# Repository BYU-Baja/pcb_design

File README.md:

# pcb_design
Design files for our custom PCB's including datasheets and custom footprints

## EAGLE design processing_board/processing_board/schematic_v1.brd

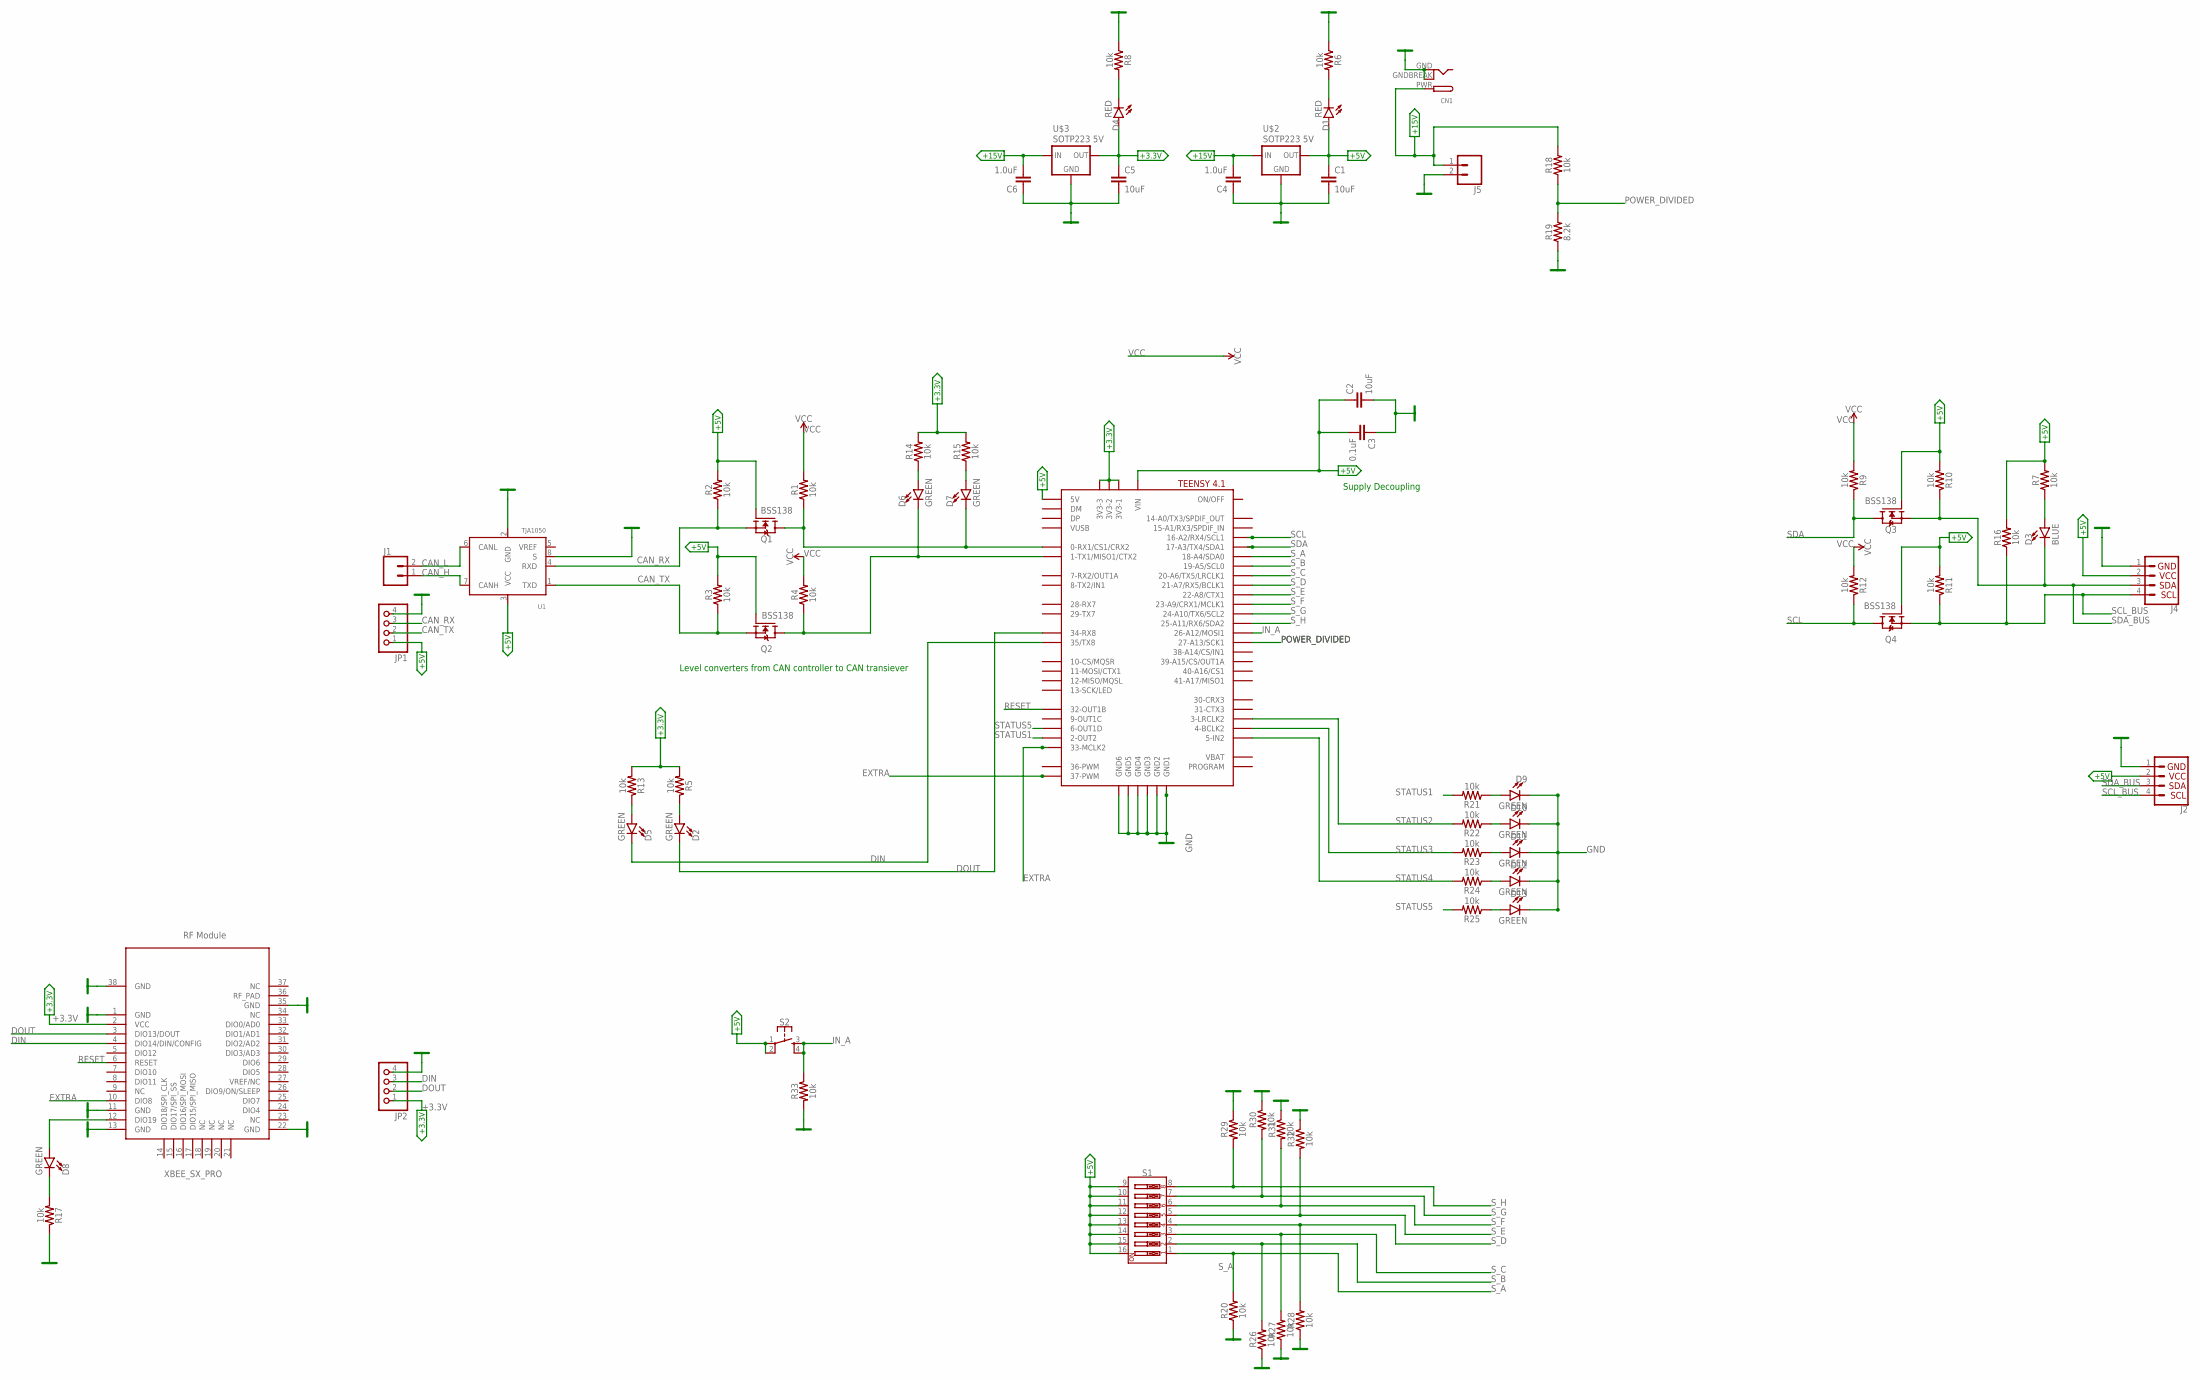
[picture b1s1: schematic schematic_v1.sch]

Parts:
C1, C2, C5: 10uF; 0603
C3: 0.1uF; 0603
C4, C6: 1.0uF; 0603
CN1: DCBARRELPTH; DCJACK_2MM_PTH
D1, D4: RED; LED-0603
D2, D5, D6, D7, D8, D9, D10, D11, D12, D13: GREEN; LED-0603
D3: BLUE; LED-0603
J1: CONN_02; 1X02
J2, J4: I2C_STANDARD; 1X04
J5: CONN_02LOCK_LONGPADS; 1X02_LOCK_LONGPADS
JP1, JP2: PINHD-1X4; 1X04
Q1, Q2, Q3, Q4: BSS138; SOT95P240X111-3N
R1, R2, R3, R4, R5, R6, R7, R8, R9, R10, R11, R12, R13, R14, R15, R16, R17, R18, R20, R21, R22, R23, R24, R25, R26, R27, R28, R29, R30, R31, R32, R33: 10k; 0603
R19: 8.2k; 0603
S1: DIP-08-PTH; DIPSWITCH-08
S2: MOMENTARY-SWITCH-SPST-2-SMD-5.2MM; TACTILE_SWITCH_SMD_5.2MM
U1: TJA1050; SOT96-1
U$1: XBEE_SX_PRO
U$2, U$3: SOTP223 5V; SOT223
U$4: TEENSY41-E; TENNSY41-E

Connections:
+3.3V: C5.1, D4.A, JP2.1, R5.2, R13.2, R14.2, R15.2, U$1.2 (VCC), U$3.2 (OUT), U$4.3V3-1, U$4.3V3-2, U$4.3V3-3
+5V: C1.1, C2.1, C3.2, D1.A, J2.2, J4.2, JP1.1, Q1.1 (G), Q2.1 (G), Q3.1 (G), Q4.1 (G), R2.2, R3.2, R7.2, R10.2, R11.2, R16.2, S1.9, S1.10, S1.11, S1.12, S1.13, S1.14, S1.15, S1.16, S2.1, S2.2, U1.3 (VCC), U$2.2 (OUT), U$4.+5V (5V), U$4.VIN
+15V: C4.2, C6.2, CN1.PWR, J5.1, R18.2, U$2.3 (IN), U$3.3 (IN)
CAN_H: J1.1, U1.7 (CANH)
CAN_L: J1.2, U1.6 (CANL)
CAN_RX: JP1.3, Q1.2 (S), R2.1, U1.4 (RXD)
CAN_TX: JP1.2, Q2.2 (S), R3.1, U1.1 (TXD)
DIN: D5.C, JP2.3, U$1.4 (DIO14/DIN/CONFIG), U$4.35-TX8 (35/TX8)
DOUT: D2.C, JP2.2, U$1.3 (DIO13/DOUT), U$4.34-RX8
EXTRA: U$1.10 (DIO8), U$4.33-MCLK2
GND: C1.2, C2.2, C3.1, C4.1, C5.2, C6.1, CN1.GND, CN1.GNDBREAK, D9.C, D10.C, D11.C, D12.C, D13.C, J2.1, J4.1, J5.2, JP1.4, JP2.4, R6.1, R8.1, R17.1, R19.1, R20.1, R26.1, R27.1, R28.1, R29.1, R30.1, R31.1, R32.1, R33.2, U1.2 (GND), U1.8 (S), U$1.1 (GND), U$1.11 (GND), U$1.13 (GND), U$1.22 (GND), U$1.35 (GND), U$1.38 (GND), U$2.1 (GND), U$3.1 (GND), U$4.GND1, U$4.GND2, U$4.GND3, U$4.GND4, U$4.GND5, U$4.GND6
IN_A: R33.1, S2.3, S2.4, U$4.26-A12/MOSI1
unnamed: D3.A, R7.1
unnamed: D7.C, Q1.3 (D), R1.1, U$4.0-RX1/CS1/CRX2
unnamed: D5.A, R13.1
unnamed: D1.C, R6.2
unnamed: D2.A, R5.1
unnamed: D4.C, R8.2
unnamed: D6.C, Q2.3 (D), R4.1, U$4.1-TX1/MISO1/CTX2
unnamed: D8.A, U$1.12 (DIO19)
unnamed: D7.A, R15.1
unnamed: D6.A, R14.1
unnamed: D9.A, R21.1
unnamed: D10.A, R22.1
unnamed: D11.A, R23.1
unnamed: D12.A, R24.1
unnamed: D13.A, R25.1
unnamed: D8.C, R17.2
POWER_DIVIDED: R18.1, R19.2, U$4.27-A13/SCK1
RESET: U$1.6 (RESET), U$4.32-OUT1B
SCL: Q4.3 (D), R12.1, U$4.16-A2/RX4/SCL1
SCL_BUS: J2.4, J4.4, Q4.2 (S), R11.1, R16.1
SDA: Q3.3 (D), R9.1, U$4.17-A3/TX4/SDA1
SDA_BUS: D3.C, J2.3, J4.3, Q3.2 (S), R10.1
STATUS1: R21.2, U$4.2-OUT2
STATUS2: R22.2, U$4.3-LRCLK2
STATUS3: R23.2, U$4.4-BCLK2
STATUS4: R24.2, U$4.5-IN2
STATUS5: R25.2, U$4.6-OUT1D
S_A: R20.2, S1.1, U$4.18-A4/SDA0
S_B: R26.2, S1.2, U$4.19-A5/SCL0
S_C: R27.2, S1.3, U$4.20-A6/TX5/LRCLK1
S_D: R28.2, S1.4, U$4.21-A7/RX5/BCLK1
S_E: R32.2, S1.5, U$4.22-A8/CTX1
S_F: R31.2, S1.6, U$4.23-A9/CRX1/MCLK1
S_G: R30.2, S1.7, U$4.24-A10/TX6/SCL2
S_H: R29.2, S1.8, U$4.25-A11/RX6/SDA2
VCC: R1.2, R4.2, R9.2, R12.2

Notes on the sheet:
Supply Decoupling
Level converters from CAN controller to CAN transiever

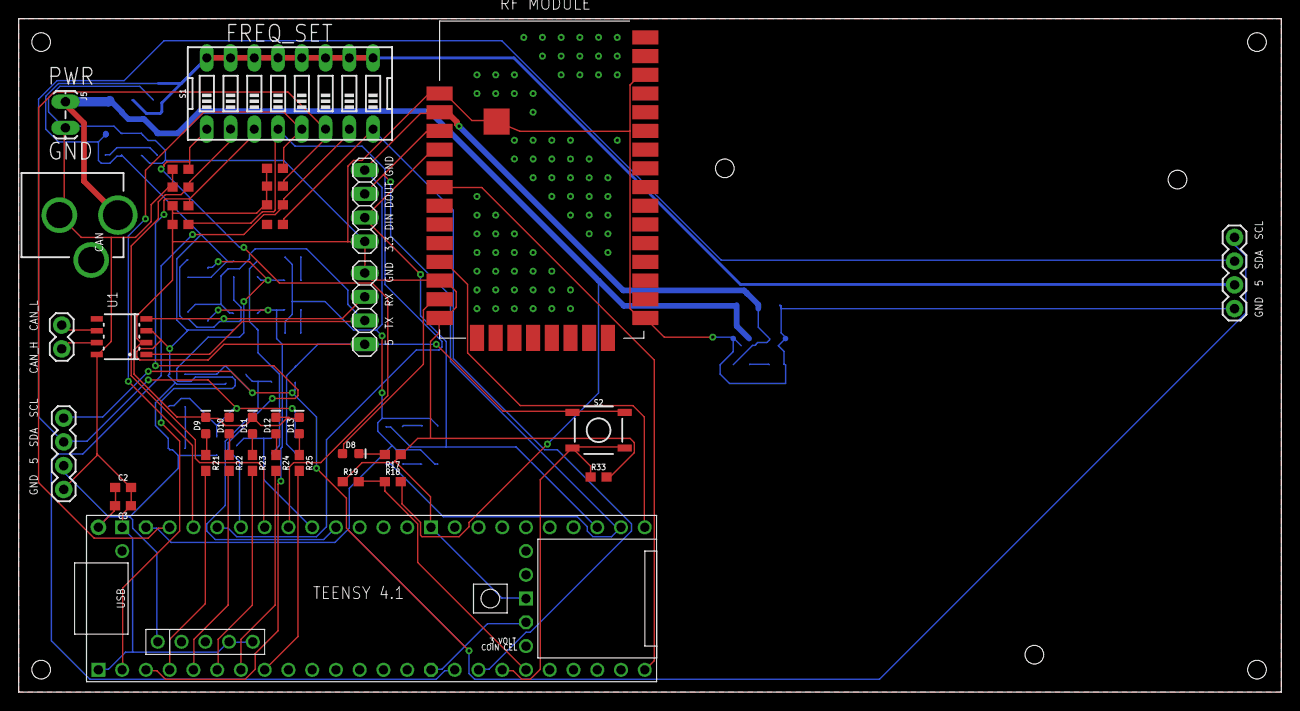
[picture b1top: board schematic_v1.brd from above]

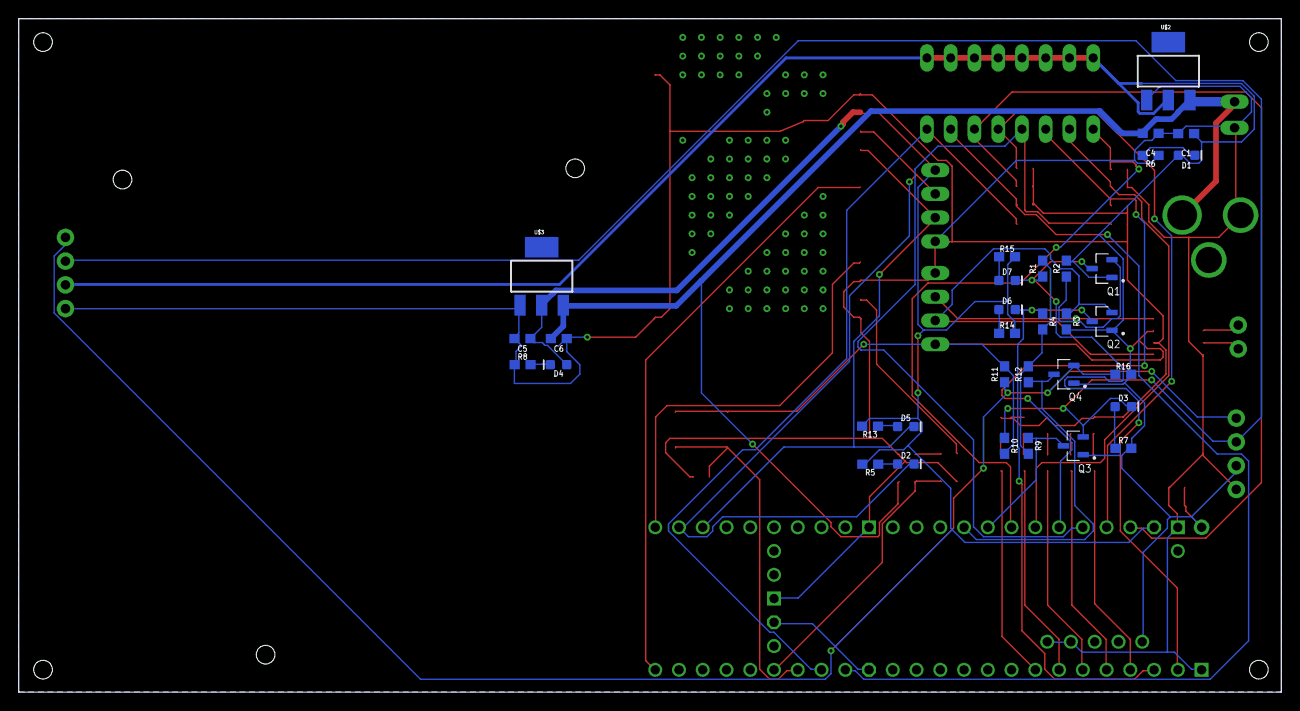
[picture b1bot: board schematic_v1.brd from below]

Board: 2 copper layers, 135.0 x 72.0 mm, 70 parts (33 on the bottom side), 48 nets.

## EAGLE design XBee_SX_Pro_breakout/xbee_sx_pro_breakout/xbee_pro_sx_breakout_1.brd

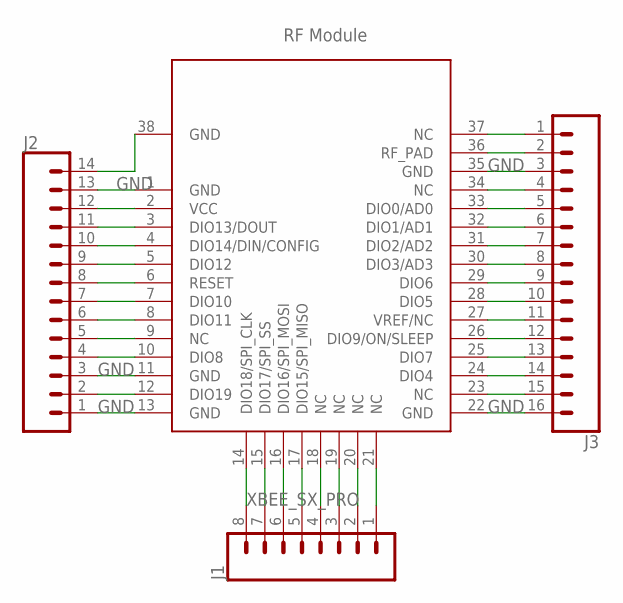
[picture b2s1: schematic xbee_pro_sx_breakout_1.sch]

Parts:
J1: CONN_08"; 1X08
J2: CONN_14; 1X14
J3: CONN_16; 1X16
U$1: XBEE_SX_PRO

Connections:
GND: J2.1, J2.3, J2.13, J2.14, J3.3, J3.16, U$1.1 (GND), U$1.11 (GND), U$1.13 (GND), U$1.22 (GND), U$1.35 (GND), U$1.38 (GND)
unnamed: J3.1, U$1.37 (NC)
unnamed: J3.2, U$1.36 (RF_PAD)
unnamed: J3.4, U$1.34 (NC)
unnamed: J3.5, U$1.33 (DIO0/AD0)
unnamed: J3.6, U$1.32 (DIO1/AD1)
unnamed: J3.7, U$1.31 (DIO2/AD2)
unnamed: J3.8, U$1.30 (DIO3/AD3)
unnamed: J3.9, U$1.29 (DIO6)
unnamed: J3.10, U$1.28 (DIO5)
unnamed: J3.11, U$1.27 (VREF/NC)
unnamed: J3.12, U$1.26 (DIO9/ON/SLEEP)
unnamed: J3.13, U$1.25 (DIO7)
unnamed: J3.14, U$1.24 (DIO4)
unnamed: J3.15, U$1.23 (NC)
unnamed: J1.1, U$1.21 (NC)
unnamed: J1.2, U$1.20 (NC)
unnamed: J1.3, U$1.19 (NC)
unnamed: J1.4, U$1.18 (NC)
unnamed: J1.5, U$1.17 (DIO15/SPI_MISO)
unnamed: J1.6, U$1.16 (DIO16/SPI_MOSI)
unnamed: J1.7, U$1.15 (DIO17/SPI_SS)
unnamed: J1.8, U$1.14 (DIO18/SPI_CLK)
unnamed: J2.2, U$1.12 (DIO19)
unnamed: J2.4, U$1.10 (DIO8)
unnamed: J2.5, U$1.9 (NC)
unnamed: J2.6, U$1.8 (DIO11)
unnamed: J2.7, U$1.7 (DIO10)
unnamed: J2.8, U$1.6 (RESET)
unnamed: J2.9, U$1.5 (DIO12)
unnamed: J2.10, U$1.4 (DIO14/DIN/CONFIG)
unnamed: J2.11, U$1.3 (DIO13/DOUT)
VCC: J2.12, U$1.2 (VCC)

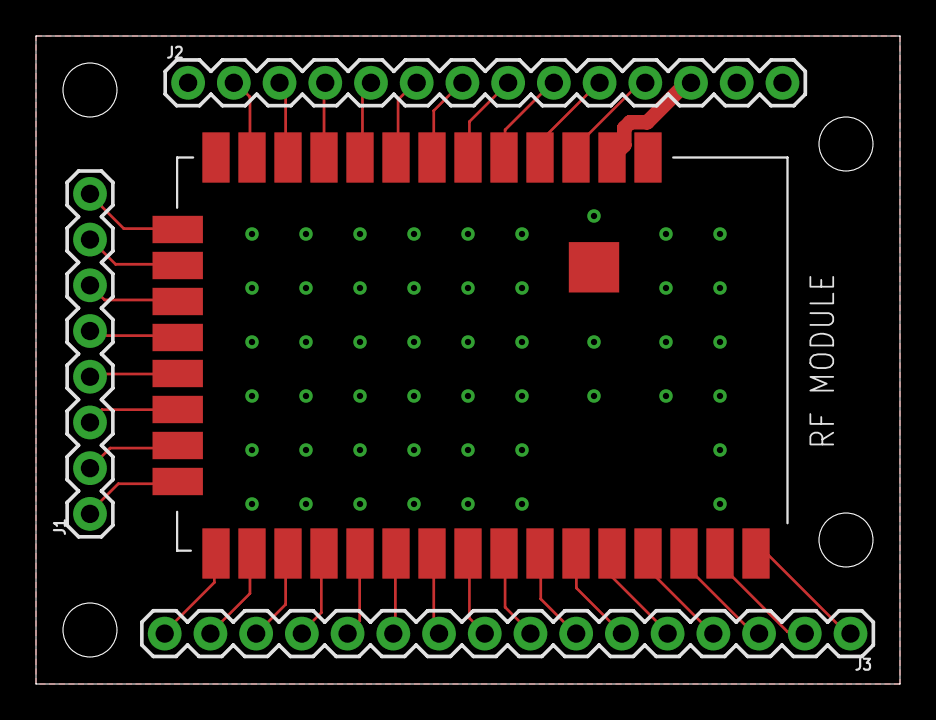
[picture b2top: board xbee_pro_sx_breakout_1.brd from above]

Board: 2 copper layers, 48.0 x 36.0 mm, 4 parts (0 on the bottom side), 33 nets.

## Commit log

2020-10-07 Initial setup
2020-10-07 added breakout project
2020-10-07 added datasheets and libraries
2020-10-07 added more libaries
2020-10-07 added sparkfun libraries
2020-10-07 started work on breakout baord
2020-10-07 added schematic
2020-10-07 added custom xbee sx pro library
2020-10-07 finished xbee library
2020-10-08 updated board
2020-10-08 board done
2020-10-08 finished breakout board
2020-10-08 updated gnd signals
2020-10-08 first round of board edit
2020-10-08 updated schematic
2020-10-08 modified shcematic and board
2020-10-09 routed to radio mod
2020-10-13 added LED
2020-11-09 upadted board
2020-11-09 new teensy 4.1 footprint
2020-11-12 pushing
2020-11-13 added arduino headers
2020-11-13 added arduino pins
2020-11-18 added dip switch
2020-11-19 fixed dip sw
2020-11-19 fixed holes
2021-01-13 added arduino
2021-01-14 finished wiring
2021-01-15 generated gerber files
2021-01-15 updated shif register
2021-03-05 3/5 updates
2021-03-08 v3 update
2021-03-29 updated pcb

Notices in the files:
parts and their libraries:
SparkFun-Connectors: Licensing: Creative Commons ShareAlike 4.0 International - https://creativecommons.org/licenses/by-sa/4.0
